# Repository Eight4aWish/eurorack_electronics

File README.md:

# Eurorack Electronics

Analog Eurorack breadboard layouts, a dual-channel low-pass gate, a mixed-signal MOD2 design (not built yet), a build-phase schematic generator, and a layout visualiser. Originally lived inside [Eight4aWish/eurorack_modules](https://github.com/Eight4aWish/eurorack_modules) — split out so that repo can stay focused on firmware.

## What's here

### `tools/n8layout/`

[n8synth](https://www.n8synth.com/) platform layout files: the official blank module templates (SVG with embedded n8 metadata) plus one worked example.

- `4HP Template.n8layout`, `6HP_Template.n8layout`, `10HP Template.n8layout`, `10HPS Template.n8layout` — official blank templates (10HPS = 10HP with a second stacked breadboard). These are the **source of truth for board geometry** — `tools/visualizer/gen_board_profiles.py` parses them into board-profile JSON.
- `808_Kick_Example.n8layout` — example 808-style kick layout

### `tools/visualizer/`

A browser-based layout viewer that renders breadboard placements from JSON, plus Python helpers for netlist → layout conversion and placement validation.

MIT ([LICENSE](tools/visualizer/LICENSE)), shared as it is. The exception is `layouts/boy_*`: they draw the analogue board, so they keep its CC BY-SA 4.0.

- `index.html` — main visualiser; opens any layout from `layouts/`
- `check.sh` — **one-command check**: geometry → net identity → browser wrapper regeneration → doc maps → doc-position cross-check. Refuses to regenerate docs from a failing layout.
- `netlist_to_layout.py` — netlist → layout JSON converter
- `smoke_test.py` — executes the visualiser's scripts against a stub DOM and asserts a layout registers; catches load-time errors that silently empty the layout picker
- `check_doc_positions.py` — every control position a doc names by hand must exist in the layout
- `edit_layout.py` — **hand-edit a layout from the bench**: move an endpoint (`b10 > g12`), set a component (`C15 = g12 g13`), mirror left/right, shift rows or ICs. Refuses any edit that would collide, then you re-run `check.sh`
- `check_netlist.py` — **every pin against a netlist**, following the wires: a row joining the wrong pins is a short, a wire left out is an open. Works on any layout, with no table to transcribe
- `cross_check_nets.py` / `validate_layout.py` / `sync_layout.py` / `gen_rowmap.py` — placement validation + maintenance helpers
- `bundle_skill.py` — copies the checks and viewer into the [n8synth-layout](https://github.com/Eight4aWish/eight4awish/tree/main/skills/n8synth-layout) Claude skill
- `gen_board_profiles.py` / `boards/` — board-profile JSON generated from the official n8synth templates: JPS control-deck cells, edge-connector maps, gap positions, D ground bus. **Ground truth for platform behaviour is [`docs/n8synth_platform.md`](docs/n8synth_platform.md)** — that document wins over anything inferred from the templates or these profiles.
- `layouts/` — per-module JS + JSON layouts

### How I use this (workflow)

The loop that produced the dual LPG, end to end:

1. **Reference review** — survey published schematics for the topology, compare sources, pick component values. Output: `docs/<module>_reference_review.md` + `docs/<module>_netlist.md` with named nets and per-source confidence tags.
2. **Skeleton layout** — `netlist_to_layout.py` converts the netlist doc into a layout JSON with components, stages, and net assignments but no positions.
3. **Placement** — fill in row/column positions per build phase (LLM-assisted in Claude Code sessions, guided by the board profile's control-deck maps in `boards/`). Panel-facing legs land on control-deck JPS pads; grounds tie to the deck-wide D bus.
4. **Verify** — `./check.sh`: zero hole collisions, every component on the nets the netlist requires, then the placement doc's row maps regenerate from the JSON so they can never drift.
5. **Build** — open the visualiser, step through the build phases at the bench; each phase carries its own test checklist (visible in the side panel).

Repeat 3–4 until clean; the layout JSON is always the single source of truth for placement.

To run locally:

```sh
# From this directory
python3 -m http.server 8000
# then open http://localhost:8000/tools/visualizer/
```

Or open `tools/visualizer/index.html` directly in a browser if you don't need module loading.

### `hardware/analogue_board/` and `tools/analogue_board/`

**The analogue board**: a general-purpose I/O board behind an n8synth Control Deck. **Rev A**, for a Teensy 4.1, was built and tested on 2026-11-01 and runs as Boy, whose firmware is in [`eurorack_modules`](https://github.com/Eight4aWish/eurorack_modules/blob/main/docs/TEENSY_MOVE.md). **Rev B**, the Pico 2 format for a Pico 2W or ESP32-P4, was ordered on 2026-11-03 (`hardware/analogue_board/pico_revb/`). Spec and decision log: [`docs/analogue_board_spec.md`](docs/analogue_board_spec.md). Rev A's firmware notes: [`docs/analogue_board_reva_firmware.md`](docs/analogue_board_reva_firmware.md). Rev B: [`docs/analogue_board_revb.md`](docs/analogue_board_revb.md).

- `hardware/analogue_board/`: the KiCad 9 project, the schematic PDF and the check results. Hardware licence CC BY-SA 4.0.
- `tools/analogue_board/build.py`: generates the schematic, runs KiCad's ERC, exports the PDF, netlist and BOM, and checks every IC pin against its datasheet, the netlist against intent, decoupling and diode orientation. See [`hardware/analogue_board/README.md`](hardware/analogue_board/README.md).

### `tools/noise_test/`

The noise comparison of five audio boards (the old Boy, Boy Rev A, the stock and OLED patch.inits, the hand-built Seed module) with the screen off, still and redrawing: `record.py` records a run through the ES-10, `analyse.py` turns it into A-weighted noise, hum, spurs and the input's share. Method, what to plug and the procedure: [`docs/noise_test.md`](docs/noise_test.md). The test firmware is in `eurorack_daisy_patch_init/noise_test` and `eurorack_modules/src/noise_test`.

### `tools/schematic/`

Build-phase schematic generator for the **Dual Pingable LPG**. Produces per-phase PNGs (Phase 1 / Phase 2 / Mix) into `docs/schematics/`, with component values read live from the LPG layout JSON so the diagrams stay in sync with the design. Built on [Schemdraw](https://schemdraw.readthedocs.io/). See [`tools/schematic/README.md`](tools/schematic/README.md).

### `docs/`

Circuit notes, netlists, and reference material.

**Plans**

- `public_tool_plan.md` — plan for a third-party-usable version of the placement/visualisation
  tooling, with the dual LPG and the MOD2/Melon hybrid as the two flagship examples.

**Platform reference**

- `n8synth_platform.md` — verified electrical behaviour of the n8synth breadboards and control
  decks: main area vs edge connector vs power rail, board variants, grounding practice. The
  single source of truth; everything else is downstream of it.

**Dual Pingable LPG** — original dual-channel low-pass gate (canonical Buchla 292 audio path + Strike + CV + Depth + mix output):

- `lpg_reference_review.md` — topology survey, target feature set, vactrol part choices
- `lpg_published_schematics.md` — comparison of the source schematics that informed the design
- `lpg_netlist.md` — full netlist
- `lpg_breadboard_placement.md` — n8synth placement, panel layout, build-phase order
- `lpg_mod_pot_rerange.md` — step-by-step bench procedure for the rev 0.27 DEPTH/MANUAL re-range (proposed, not yet built), written for picking the board up cold
- `lpg_bom.csv` — bill of materials
- `schematics/` — generated build-phase PNGs

Reference materials that informed the LPG design are linked at their original sources (see Credits) rather than redistributed here.

## Credits

### Dual Pingable LPG

The audio path is the canonical **Buchla 292** Lopass Gate, originally designed by **Don Buchla** (~1971). The topology, component values, and driver structure of this build were cross-validated against multiple independent published sources, each linked at its original home:

- **Parker, J. & D'Angelo, S.** — *"A Digital Model of the Buchla Lowpass-Gate"*, [DAFx 2013](https://www.dafx.de/paper-archive/details.php?id=uqLQLFI9j52bBmv10UKKMg) — the analytic topology and closed-form gains (Rα placement per Eq. 4 / Eq. 12).
- **Nonlinear Circuits (NLC) [Low Pass Gate](https://www.nonlinearcircuits.com/modules/p/low-pass-gate)** — Rα = 4M7, 470R LED current limit, the zener clamp on the LED-drive node (VD5 / VD6).
- **AI Synthesis [AI017 Low Pass Gate](https://aisynthesis.com/product/ai017-low-pass-gate/)** — 10K series resistors flanking the vactrol LDRs, DEPTH wired as a rheostat (their P3).
- **Eddy Bergmann's redrawn Buchla 292** — [Synthesizer Build part-35: Resonant Lopass Gate](https://www.eddybergman.com/2020/10/synthesizer-build-part-35-resonant.html) — confirmed the Rα placement and the 1K series output resistor (R_OUT_A / R_OUT_B).
- **Thomas White's [NRM Lopass Gate](https://modularsynthesis.com/nrm/lopass/lopass.htm)** — third independent confirmation of Rα at V₊ → GND.
- **Doepfer [A-101-2 Low Pass Gate](https://doepfer.de/a1012.htm)** — the "status LED tracks vactrol drive" concept (adapted here to a parallel branch off the driver, rather than series, for compatibility across vactrol / LED options).

Target feature set (dual-channel, Strike-pingable, no DAMP / mode-switch in the day-one core) follows the **Make Noise Optomix / LxD** shape; see [lpg_reference_review.md](docs/lpg_reference_review.md) for the topology survey and trade-offs. Per-source confidence tags and the rationale for each block are in [lpg_netlist.md](docs/lpg_netlist.md) and [lpg_published_schematics.md](docs/lpg_published_schematics.md).

## Companion repo

Firmware for Eurorack modules using these analog voices and layouts lives in [Eight4aWish/eurorack_modules](https://github.com/Eight4aWish/eurorack_modules). Per-module pre-built binaries are published as releases there.

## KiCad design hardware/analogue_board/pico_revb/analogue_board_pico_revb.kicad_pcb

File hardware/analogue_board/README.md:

# Analogue boards, Rev A

General-purpose Eurorack I/O boards. A compute module sits on headers on one side, an n8synth
Control Deck on the other, and every audio, CV, gate, pot and display interface sits in between.
Rev A is **two boards** from one design (2026-10-16):

| Board | Module | Folder |
|---|---|---|
| Pico board | Raspberry Pi Pico 2, or a Waveshare ESP32-P4-WIFI6 in its pinout | [`pico/`](pico/) |
| Teensy board | Teensy 4.1, all 48 pins on standard headers | [`teensy/`](teensy/) |

Both boards share the peripheral circuits, pin functions, wiring field, edge strips and power
corner, so firmware and panel wiring are the same on both. The design brief and every decision
behind it are in [`docs/analogue_board_spec.md`](../../docs/analogue_board_spec.md).

Two more builds from the same generator are routing trials, not boards to order:

| Trial | What it is | Folder |
|---|---|---|
| Shared board | Both module footprints interleaved on one board, as checkpoint 2 had it; the Teensy on shortened headers | [`shared/`](shared/) |
| Core board | The Pico board without the fixed-direction CV channels, TRS MIDI or the Qwiic socket, with six pots; parts 0.4 mm apart, 0.127 mm signal rules. The first to route (spec §14); its routed board is in [`pico_core/routed_trial/`](pico_core/routed_trial/) | [`pico_core/`](pico_core/) |
| Shared core board | Both module sockets (the Teensy on full headers), TRS MIDI, the display on I2C holes, six switchable CV jacks, six pots, four gates each way. Four routes in a row ended 2 connections short, a different 2 each time; its first routed board is in [`shared_core/routed_trial/`](shared_core/routed_trial/) | [`shared_core/`](shared_core/) |
| **Pico core board with MIDI** | The same feature set on a Pico 2 / ESP32-P4 board alone: module 8 mm lower, no bus test points, +5VD plane on In4, top of the board re-laid by David with no chip over another. **Fully routed** (0 unconnected, 0 copper faults); routed board in [`pico_core_midi/routed_trial/`](pico_core_midi/routed_trial/), order files in [`pico_core_midi/fab/`](pico_core_midi/fab/), held until the Teensy board is brought up | [`pico_core_midi/`](pico_core_midi/) |
| **Teensy core board with MIDI** | **The first board to route completely:** the same feature set on a Teensy 4.1 board alone, placement revised by eye. 0 unconnected, 0 copper faults; its routed board is in [`teensy_core_midi/routed_trial/`](teensy_core_midi/routed_trial/) | [`teensy_core_midi/`](teensy_core_midi/) |
| **Rev B, Pico 2 / ESP32-P4** | Laid out panel first ([`docs/analogue_board_revb.md`](../../docs/analogue_board_revb.md)): one wiring template level with the deck's cells, the ESP32-P4's own I2C reserved, 10HP only, the power header in the lower gap. **Fully routed** (0 unconnected, 0 copper faults, every IC supply pin within 4 mm of a capacitor); routed board in [`pico_revb/routed_trial/`](pico_revb/routed_trial/). Order after the Teensy board's bring-up | [`pico_revb/`](pico_revb/) |

**Status: checkpoint 4, 2026-10-16.** `teensy_core_midi` routes completely: KiCad's DRC finds
no unconnected item and no copper fault, every surface-mount ground pad has its own via to the
plane, and 54 decoupling capacitors are wired straight to their pins. Its wiring blocks and test
points are labelled, the wiring map is in `teensy_core_midi/output/wiring_map.md`, and the JLCPCB
files are in [`teensy_core_midi/fab/`](teensy_core_midi/fab/): **ordered 2026-10-16** (5 boards,
2 assembled). `pico_core_midi` routes completely too (2026-10-17); its order waits on the Teensy
board's bring-up, so any Rev A lessons go into it first. The spec's §14 has every trial; the
story is in [`docs/analogue_board_journal.md`](../../docs/analogue_board_journal.md).
- **Schematic history:** it passed checkpoint 1 as a single board with both module footprints.
  The split changed only the root sheet (one module) and the power sheet, where the ESP32-P4
  bypass (Q201, JP201) stays on the Pico board.

## What's here

| File | What it is |
|---|---|
| `pico/`, `teensy/` | One KiCad 9 project per board. Each folder holds: |
| ↳ `analogue_board_<board>_schematic.pdf` | The schematic, 10 A3 sheets. Sheet 1 is the module and its pin map |
| ↳ `analogue_board_<board>.kicad_pcb` | Checkpoint 3: every part placed on both faces; not yet routed |
| ↳ `output/placement_outward_face.pdf`, `output/placement_deck_face.pdf` | Placement drawings: every part's outline, pads and reference, one face per PDF (vector, zoom in). The deck face is mirrored, as seen from the deck side |
| ↳ `output/placement_outward_face.png`, `output/placement_deck_face.png` | 3D renders of both faces (the deck face seen from below, so mirrored) |
| ↳ `output/checks.md` | Every checkpoint-1 check and its result: ERC, netlist, pins against datasheets, footprints, decoupling, diode orientation |
| ↳ `output/erc.rpt`, `output/*.net`, `output/*_bom.csv` | KiCad's ERC report, netlist and grouped BOM with LCSC numbers |
| `analogue_board.kicad_sym`, `analogue_board.pretty/` | Project symbols and footprints, shared by both boards: DAC8568, Pico 2, Teensy 4.1, edge strip, module sockets, edge strips, wiring holes |
| [`boards_printout.pdf`](boards_printout.pdf) | 1:1 printout (A4, print at 100 %) of each board's outline, edge strips, module socket, USB keep-out and power header, to lay real parts on |
| [`checkpoint2_printout.pdf`](checkpoint2_printout.pdf) | The checkpoint 2 printout, from when both modules shared one board (kept as the record) |
| [`LICENSE`](LICENSE) | CC BY-SA 4.0 |

## The boards are generated

The KiCad files are written by [`tools/analogue_board/`](../../tools/analogue_board/). Change the
generator, not the KiCad files, until the boards are signed off. After that the KiCad files
become the source and the generator is retired.

```sh
python3 tools/analogue_board/build.py      # schematics, ERC, netlists, PDFs, checks (both boards)
python3 tools/analogue_board/pcb.py        # the boards: placement, DRC, renders (both boards)
python3 tools/analogue_board/build.py teensy   # or one board: pico or teensy
```

`build.py` regenerates the libraries and all ten sheets. It then runs KiCad's ERC, exports the
PDF, netlist and BOM through `kicad-cli`, and runs the checks. It exits non-zero if any check
fails. It needs KiCad 9 at `/Applications/KiCad` and Python 3, nothing else.

| Generator file | Holds |
|---|---|
| `variant.py` | Which board a run builds (`pico`, `teensy`, the trials `shared`, `pico_core`, `shared_core`, `pico_core_midi` and `teensy_core_midi`, and Rev B's `pico_revb`): folders, module sockets, feature set, placement spacing, track rules, the module's position and the power header's |
| `design.py` | Pin map, root sheet (this board's module), power sheet |
| `design_analog.py` | Codec and audio, CV jacks and ADC, CV DAC |
| `design_digital.py` | Pots and gate outs, expander/I2C/LEDs, gate ins and jack detect, edge strips, TRS MIDI |
| `parts.py` | Every part: symbol, footprint, LCSC number, datasheet |
| `datasheet_pins.json` | Each IC's pinout transcribed from its datasheet, independently of KiCad's library. `checks.py` compares the two. |
| `checks.py` | The checkpoint-1 checks |
| `placement.py` | Geometry: outline, strips, module positions, keep-outs, power header, and each board's floorplan |
| `wiring.py` | The wiring field: every channel hole, its bank (four mixed banks, one per quarter of the board) and its slot. The schematic and the placement both read it |
| `pcb.py` | Writes each board from its netlist and `placement.py`. It prints the area budget, runs DRC with the schematic-parity check, checks part heights and renders both faces |
| `autoplace.py` | First-pass placement of every part `placement.py` does not anchor, as close as it fits to the pins it connects to |
| `autoroute.py` | Autoroute with Freerouting. Runs under KiCad's Python and writes a separate trial board in `<board>/output/autoroute/` (not committed). Takes 4 or 6 layers, a run label and any Freerouting setting. `--staged` runs the stages (`--stages=2` stops after the second); `--ground-vias` gives every surface-mount ground pad its own via first, `--decoupling` wires each decoupling capacitor to its pin first; `--lock-existing` and `--unlock` set what the router may rip up. Freerouting's analytics are switched off |
| `finish.py` | Finishes a routed board: via drills, narrow tracks, copper faults taken up, the leftover connections routed by its own grid router and then by rip-up and reroute, dead ends removed, ground pads stitched. Also holds the pre-route steps `autoroute.py` calls |
| `labels.py` | Silkscreen on a routed board: block numbers W1, W2 ... beside the wiring blocks, short names beside the test points; writes `output/wiring_map.md` (every block's holes and signals, every test point) and 1:1 PDFs of each face to print |
| `fab.py` | JLCPCB files from a finished board: Gerbers and drill zipped, BOM and placement (CPL) in JLC's format, into `<board>/fab/` |
| `printout.py` | Writes `boards_printout.pdf` |

The netlist check works from intent. Every connection the generator draws is also recorded as
"pin X belongs on net Y". The check then compares those records with the netlist KiCad computes.
A wire that lands on the wrong pin, two nets that touch, or a pin nobody meant to connect all
fail the build.

## Wiring field conventions

- Every wiring hole is round, except **ground holes, which are square**.
- The headers keep KiCad's square pin 1: the module socket, the edge strips' outer holes, and
  J201, where pin 1 is −12 V (the red stripe).

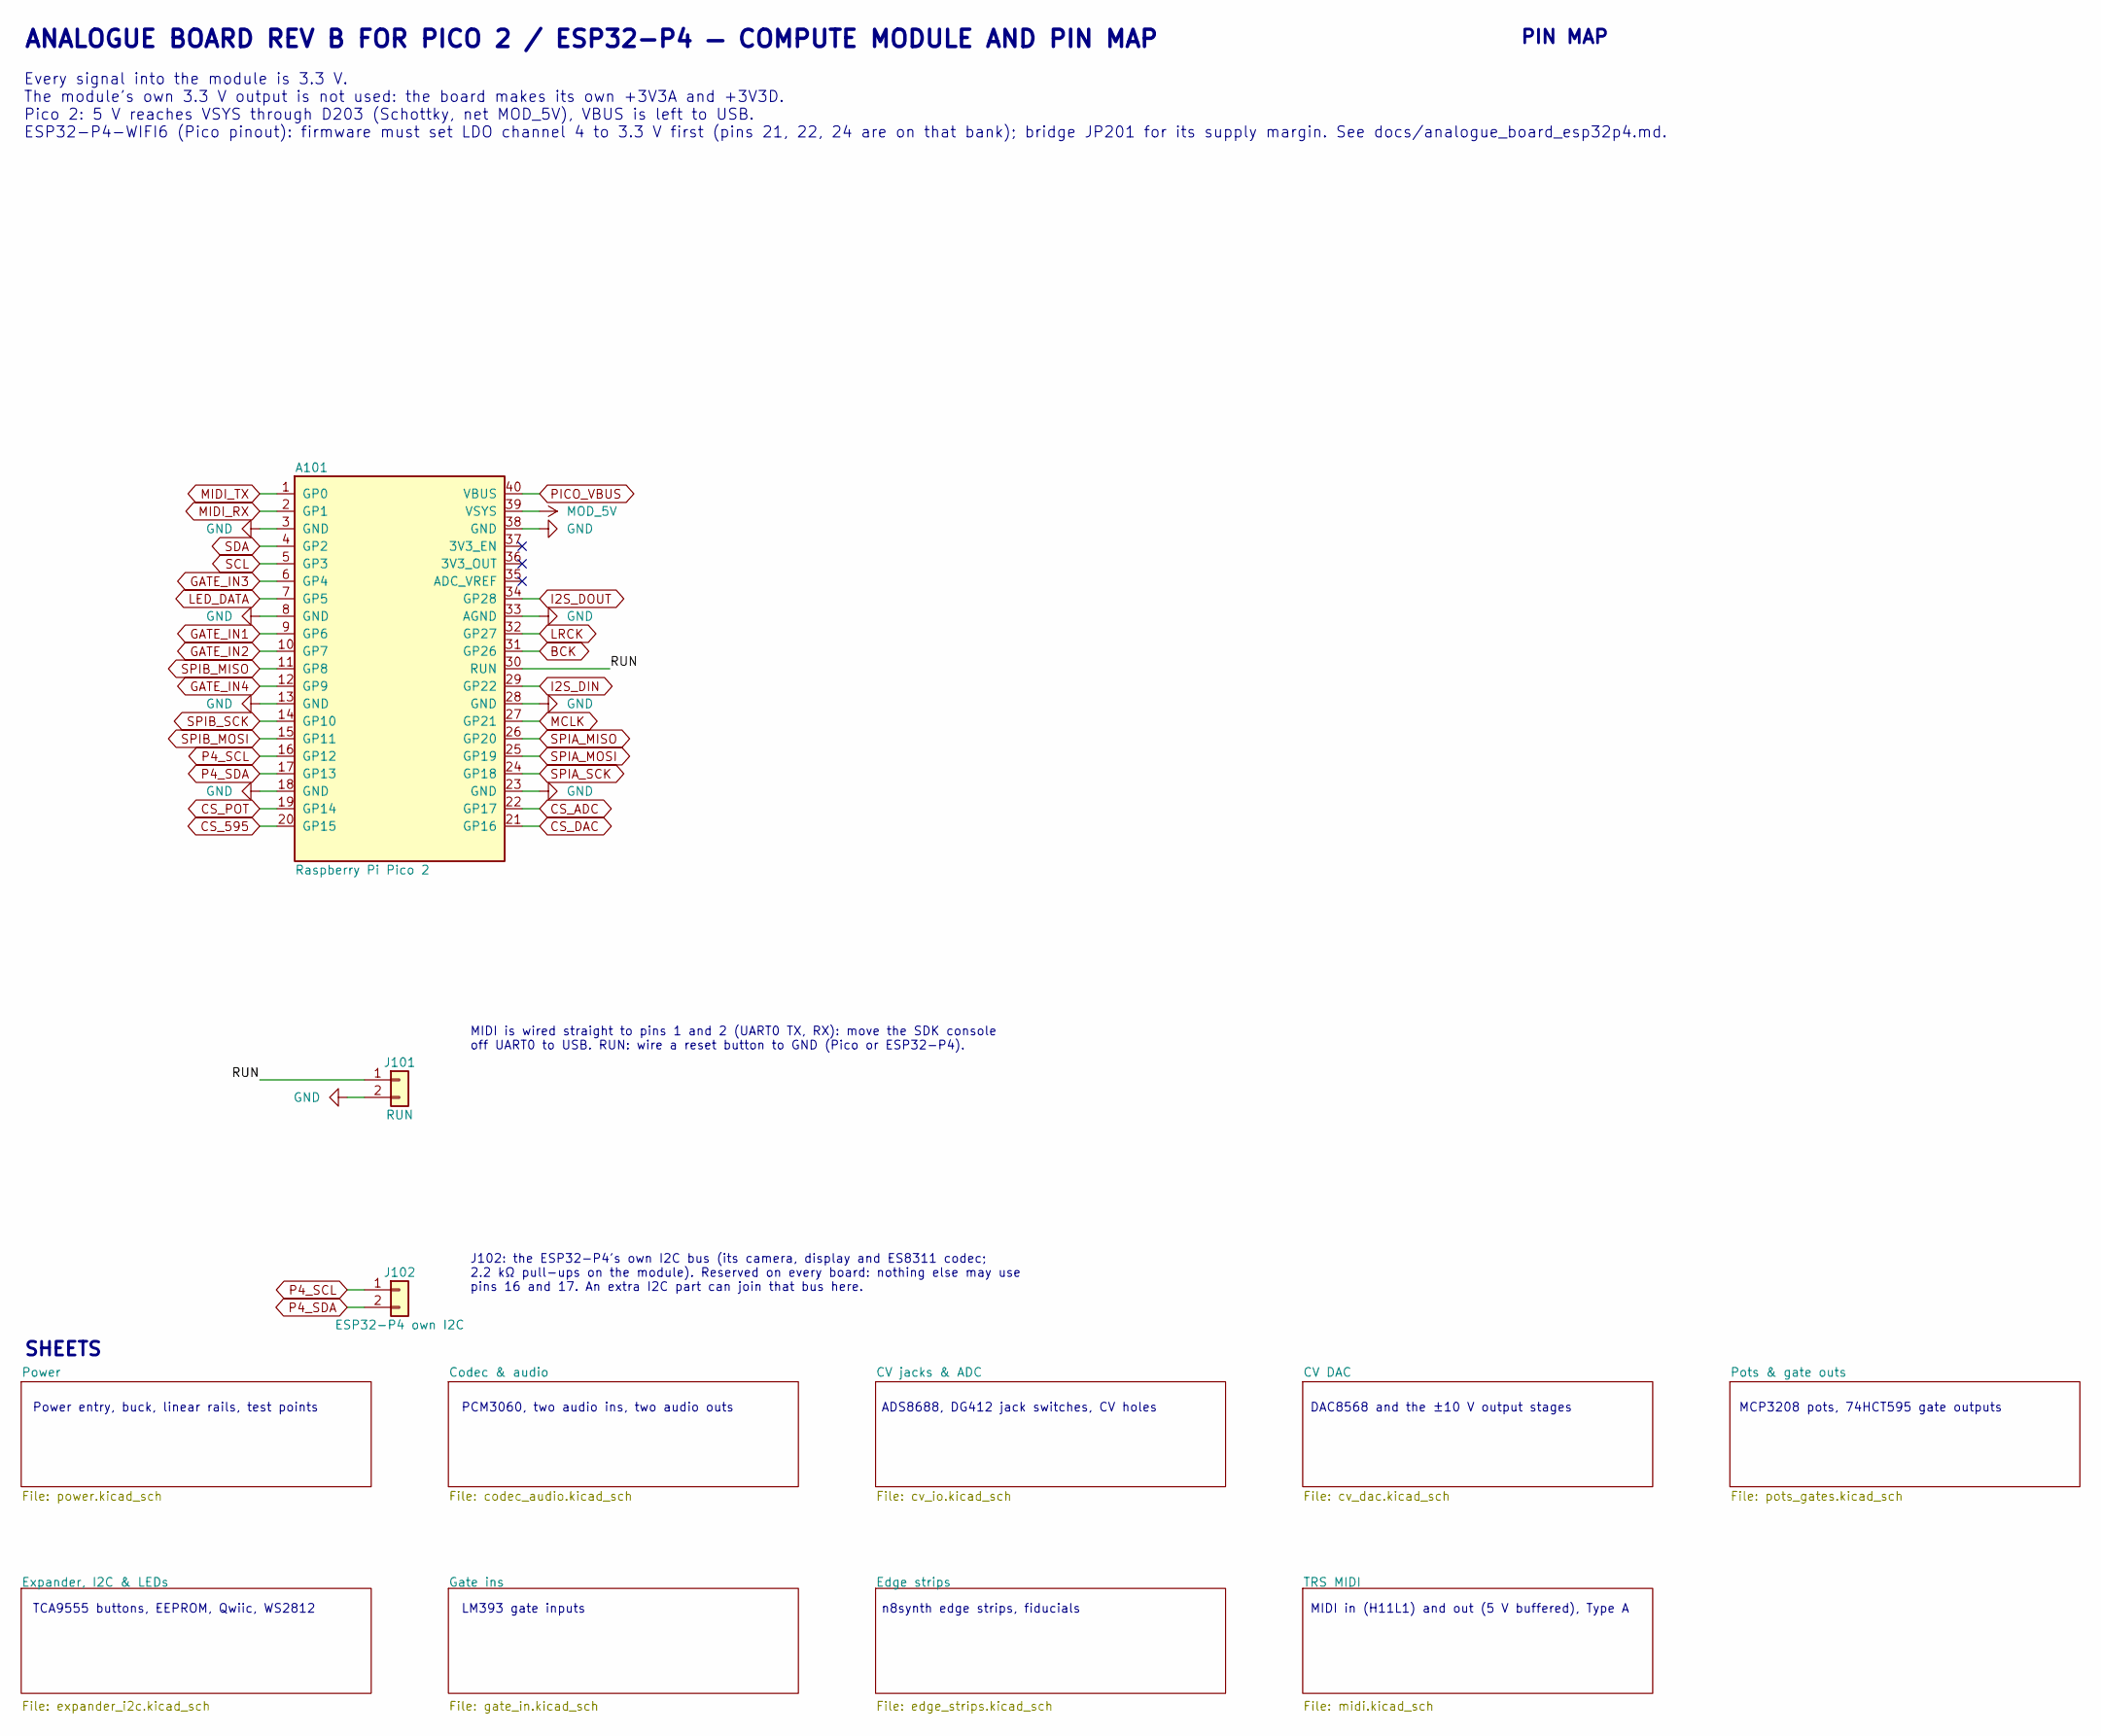
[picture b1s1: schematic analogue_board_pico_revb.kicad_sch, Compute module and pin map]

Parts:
A101: Raspberry Pi Pico 2; Pico2_Socket; MPN SC1631 on 2x20 female headers; JLC hand-soldered
J101: RUN; WiringHoles_1x02_G2; JLC bare holes
J102: ESP32-P4 own I2C; WiringHoles_1x02; JLC bare holes

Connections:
/RUN: A101.30 (RUN), J101.1
BCK: A101.31 (GP26); also elsewhere on the board
CS_595: A101.20 (GP15); also elsewhere on the board
CS_ADC: A101.22 (GP17); also elsewhere on the board
CS_DAC: A101.21 (GP16); also elsewhere on the board
CS_POT: A101.19 (GP14); also elsewhere on the board
GATE_IN1: A101.9 (GP6); also elsewhere on the board
GATE_IN2: A101.10 (GP7); also elsewhere on the board
GATE_IN3: A101.6 (GP4); also elsewhere on the board
GATE_IN4: A101.12 (GP9); also elsewhere on the board
GND: A101.3 (GND), A101.8 (GND), A101.13 (GND), A101.18 (GND), A101.23 (GND), A101.28 (GND), A101.33 (AGND), A101.38 (GND), J101.2; also elsewhere on the board
I2S_DIN: A101.29 (GP22); also elsewhere on the board
I2S_DOUT: A101.34 (GP28); also elsewhere on the board
LED_DATA: A101.7 (GP5); also elsewhere on the board
LRCK: A101.32 (GP27); also elsewhere on the board
MCLK: A101.27 (GP21); also elsewhere on the board
MIDI_RX: A101.2 (GP1); also elsewhere on the board
MIDI_TX: A101.1 (GP0); also elsewhere on the board
MOD_5V: A101.39 (VSYS); also elsewhere on the board
P4_SCL: A101.16 (GP12), J102.1
P4_SDA: A101.17 (GP13), J102.2
PICO_VBUS: A101.40 (VBUS); also elsewhere on the board
SCL: A101.5 (GP3); also elsewhere on the board
SDA: A101.4 (GP2); also elsewhere on the board
SPIA_MISO: A101.26 (GP20); also elsewhere on the board
SPIA_MOSI: A101.25 (GP19); also elsewhere on the board
SPIA_SCK: A101.24 (GP18); also elsewhere on the board
SPIB_MISO: A101.11 (GP8); also elsewhere on the board
SPIB_MOSI: A101.15 (GP11); also elsewhere on the board
SPIB_SCK: A101.14 (GP10); also elsewhere on the board

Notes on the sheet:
ANALOGUE BOARD REV B FOR PICO 2 / ESP32-P4 — COMPUTE MODULE AND PIN MAP
Every signal into the module is 3.3 V. The module's own 3.3 V output is not used: the board makes its own +3V3A and +3V3D. Pico 2: 5 V reaches VSYS through D203 (Schottky, net MOD_5V), VBUS is left to USB. ESP32-P4-WIFI6 (Pico pinout): firmware must set LDO channel 4 to 3.3 V first (pins 21, 22, 24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
MIDI is wired straight to pins 1 and 2 (UART0 TX, RX): move the SDK console off UART0 to USB. RUN: wire a reset button to GND (Pico or ESP32-P4).
J102: the ESP32-P4's own I2C bus (its camera, display and ES8311 codec; 2.2 kΩ pull-ups on the module). Reserved on every board: nothing else may use pins 16 and 17. An extra I2C part can join that bus here.
PIN MAP
Power entry, buck, linear rails, test points
PCM3060, two audio ins, two audio outs
ADS8688, DG412 jack switches, CV holes
DAC8568 and the ±10 V output stages
MCP3208 pots, 74HCT595 gate outputs
TCA9555 buttons, EEPROM, Qwiic, WS2812
LM393 gate inputs
n8synth edge strips, fiducials
MIDI in (H11L1) and out (5 V buffered), Type A
SHEETS

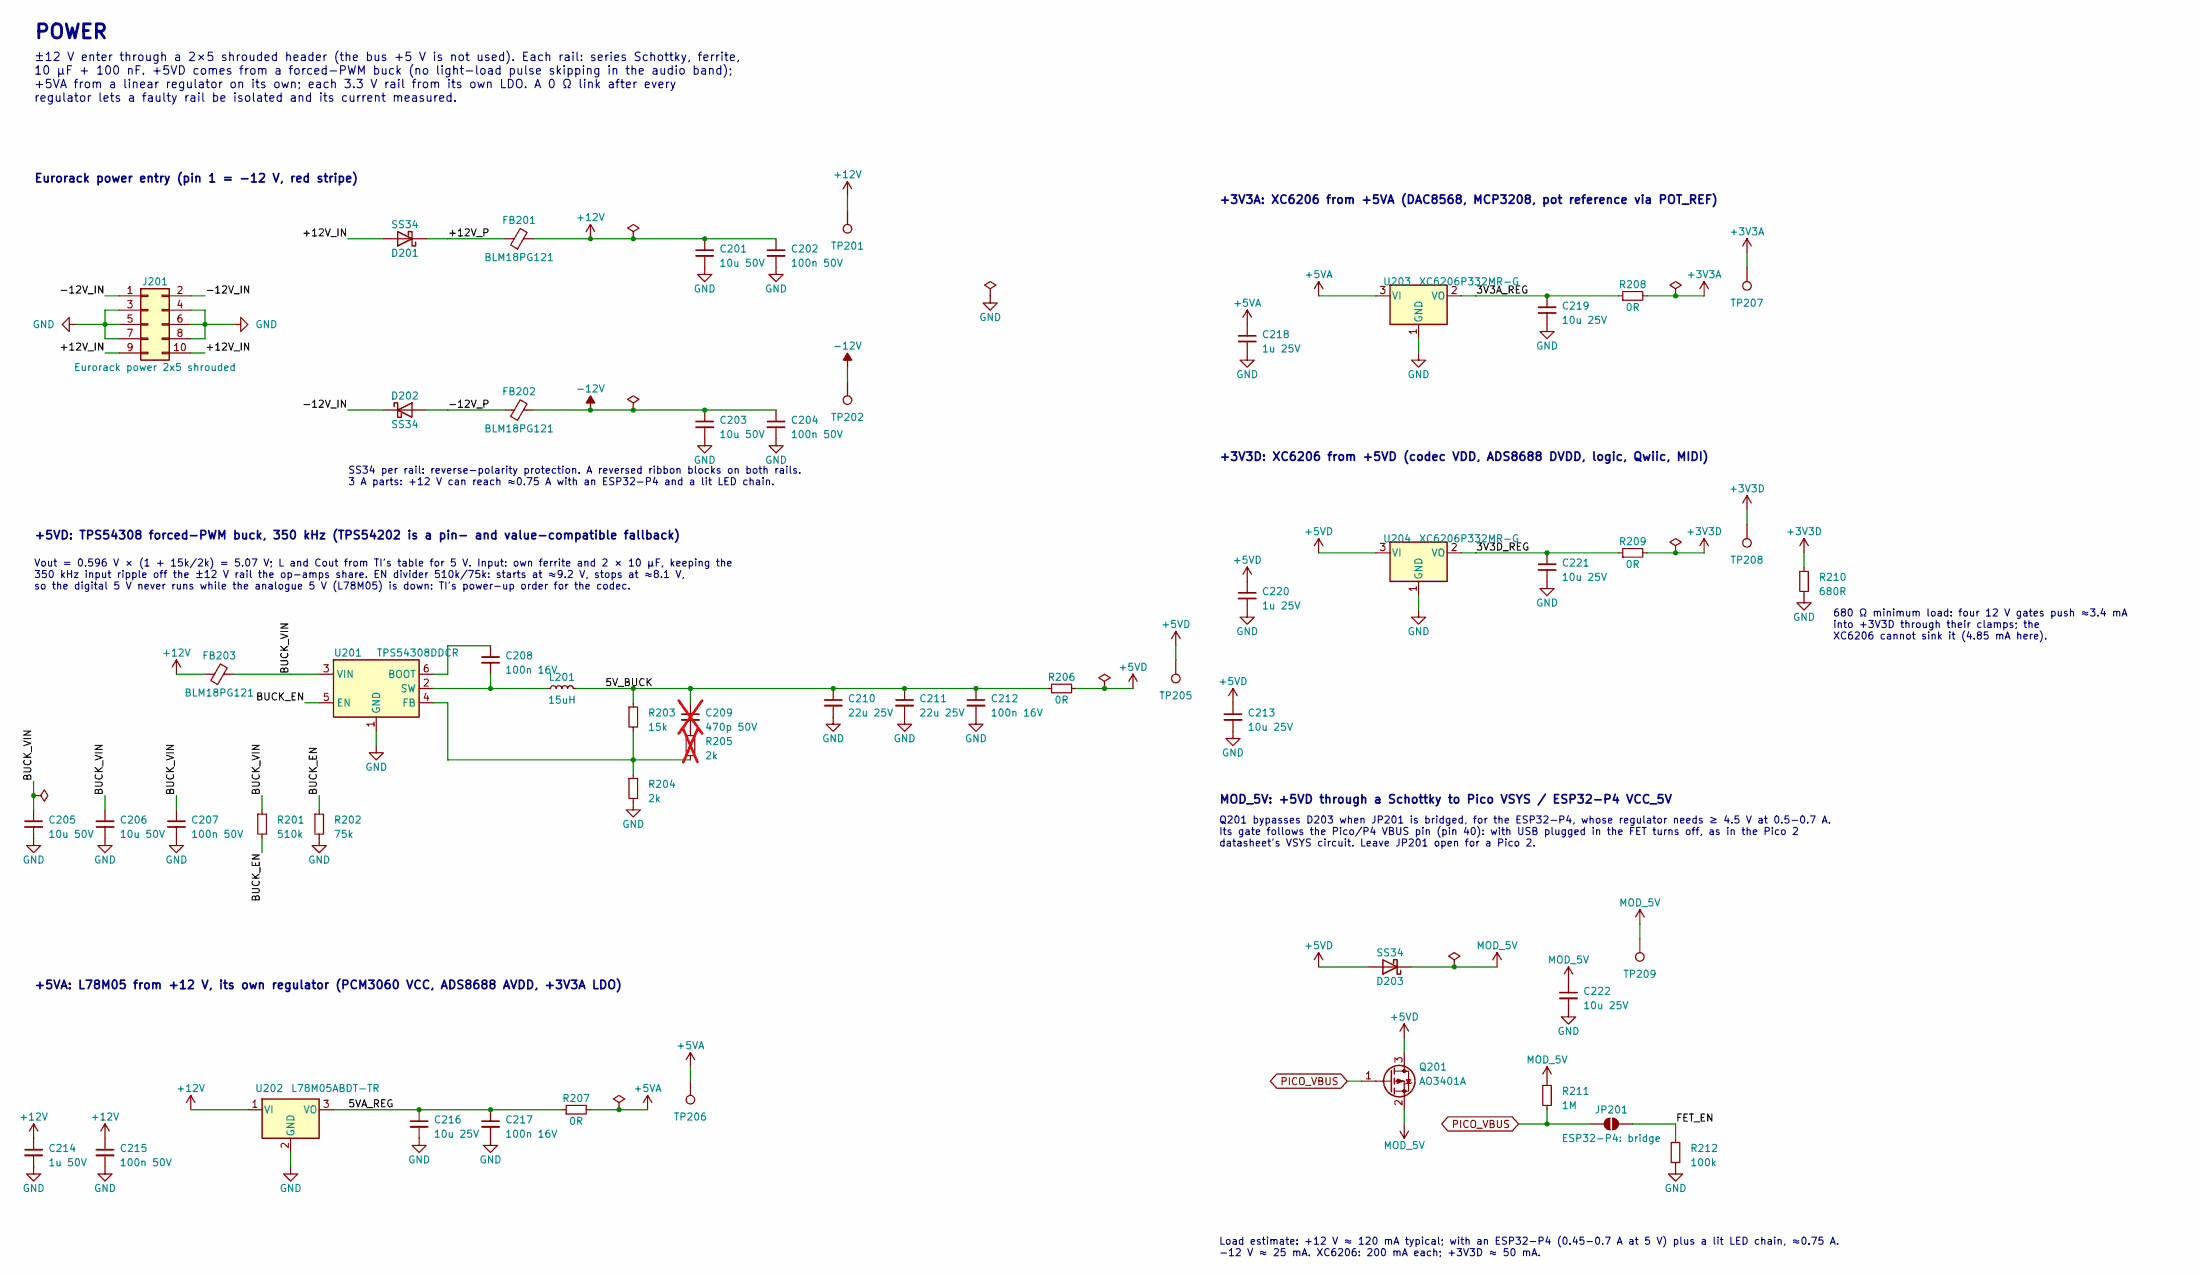
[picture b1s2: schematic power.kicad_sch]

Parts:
C201, C203, C205, C206: 10u 50V; C_1206_3216Metric; Voltage 50V; LCSC C13585
C202, C204, C207, C215: 100n 50V; C_0603_1608Metric; Voltage 50V; LCSC C14663
C208, C212, C217: 100n 16V; C_0402_1005Metric; Voltage 16V; LCSC C1525
C209: 470p 50V; C_0402_1005Metric; Voltage 50V; JLC not fitted; not fitted
C210, C211: 22u 25V; C_1206_3216Metric; Voltage 25V; LCSC C12891
C213, C216, C219, C221, C222: 10u 25V; C_0805_2012Metric; Voltage 25V; LCSC C15850
C214: 1u 50V; C_0603_1608Metric; Voltage 50V; LCSC C15849
C218, C220: 1u 25V; C_0402_1005Metric; Voltage 25V; LCSC C52923
D201, D202, D203: SS34; D_SMA; MPN SS34; LCSC C8678
FB201, FB202, FB203: BLM18PG121; L_0603_1608Metric; MPN BLM18PG121SN1D; LCSC C14709
J201: Eurorack power 2x5 shrouded; IDC-Header_2x05_P2.54mm_Vertical; MPN 2x5 2.54 mm shrouded box header; JLC hand-soldered
JP201: ESP32-P4: bridge; SolderJumper-2_P1.3mm_Open_RoundedPad1.0x1.5mm; JLC bare pad
L201: 15uH; L_Sunlord_SWPA5040S; MPN SWPA5040S150MT; LCSC C44888
Q201: AO3401A; SOT-23; MPN AO3401A; LCSC C15127
R201: 510k; R_0603_1608Metric; Tolerance 1%; LCSC C23192
R202: 75k; R_0603_1608Metric; Tolerance 1%; LCSC C23242
R203: 15k; R_0402_1005Metric; Tolerance 1%; LCSC C25756
R204: 2k; R_0402_1005Metric; Tolerance 1%; LCSC C4109
R205: 2k; R_0402_1005Metric; Tolerance 1%; LCSC C4109; not fitted
R206: 0R; R_0805_2012Metric; Tolerance 1%; LCSC C17477
R207, R208, R209: 0R; R_0603_1608Metric; Tolerance 1%; LCSC C21189
R210: 680R; R_0603_1608Metric; Tolerance 1%; LCSC C23228
R211: 1M; R_0402_1005Metric; Tolerance 1%; LCSC C26083
R212: 100k; R_0402_1005Metric; Tolerance 1%; LCSC C25741
TP201: +12V; TestPoint_Pad_D1.0mm; JLC bare pad
TP202: -12V; TestPoint_Pad_D1.0mm; JLC bare pad
TP205: +5VD; TestPoint_Pad_D1.0mm; JLC bare pad
TP206: +5VA; TestPoint_Pad_D1.0mm; JLC bare pad
TP207: +3V3A; TestPoint_Pad_D1.0mm; JLC bare pad
TP208: +3V3D; TestPoint_Pad_D1.0mm; JLC bare pad
TP209: MOD_5V; TestPoint_Pad_D1.0mm; JLC bare pad
U201: TPS54308DDCR; SOT-23-6; MPN TPS54308DDCR; LCSC C168839
U202: L78M05ABDT-TR; TO-252-2_PasteShapes; MPN L78M05ABDT-TR; LCSC C58069
U203, U204: XC6206P332MR-G; SOT-23; MPN XC6206P332MR-G; LCSC C5446

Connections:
+3V3A: R208.2, TP207.1; also elsewhere on the board
+3V3D: R209.2, R210.1, TP208.1; also elsewhere on the board
+5VA: C218.1, R207.2, TP206.1, U203.3 (VI); also elsewhere on the board
+5VD: C213.1, C220.1, D203.2 (A), Q201.3 (D), R206.2, TP205.1, U204.3 (VI); also elsewhere on the board
+12V: C201.1, C202.1, C214.1, C215.1, FB201.2, FB203.1, TP201.1, U202.1 (VI); also elsewhere on the board
-12V: C203.1, C204.1, FB202.2, TP202.1; also elsewhere on the board
/Power/3V3A_REG: C219.1, R208.1, U203.2 (VO)
/Power/3V3D_REG: C221.1, R209.1, U204.2 (VO)
/Power/5VA_REG: C216.1, C217.1, R207.1, U202.3 (VO)
/Power/5V_BUCK: C209.1, C210.1, C211.1, C212.1, L201.2, R203.1, R206.1
/Power/+12V_IN: D201.2 (A), J201.9, J201.10
/Power/+12V_P: D201.1 (K), FB201.1
/Power/-12V_IN: D202.1 (K), J201.1, J201.2
/Power/-12V_P: D202.2 (A), FB202.1
/Power/BUCK_EN: R201.2, R202.1, U201.5 (EN)
/Power/BUCK_VIN: C205.1, C206.1, C207.1, FB203.2, R201.1, U201.3 (VIN)
/Power/FET_EN: JP201.2 (B), R212.1
GND: C201.2, C202.2, C203.2, C204.2, C205.2, C206.2, C207.2, C210.2, C211.2, C212.2, C213.2, C214.2, C215.2, C216.2, C217.2, C218.2, C219.2, C220.2, C221.2, C222.2, J201.3, J201.4, J201.5, J201.6, J201.7, J201.8, R202.2, R204.2, R210.2, R212.2, U201.1 (GND), U202.2 (GND), U203.1 (GND), U204.1 (GND); also elsewhere on the board
MOD_5V: C222.1, D203.1 (K), Q201.2 (S), R211.1, TP209.1; also elsewhere on the board
unnamed: C209.2, R205.1
unnamed: C208.1, U201.6 (BOOT)
unnamed: R203.2, R204.1, R205.2, U201.4 (FB)
unnamed: C208.2, L201.1, U201.2 (SW)
PICO_VBUS: JP201.1 (A), Q201.1 (G), R211.2; also elsewhere on the board

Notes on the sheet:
POWER
±12 V enter through a 2×5 shrouded header (the bus +5 V is not used). Each rail: series Schottky, ferrite, 10 µF + 100 nF. +5VD comes from a forced-PWM buck (no light-load pulse skipping in the audio band); +5VA from a linear regulator on its own; each 3.3 V rail from its own LDO. A 0 Ω link after 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
Eurorack power entry (pin 1 = -12 V, red stripe)
SS34 per rail: reverse-polarity protection. A reversed ribbon blocks on both rails. 3 A parts: +12 V can reach ≈0.75 A with an ESP32-P4 and a lit LED chain.
+5VD: TPS54308 forced-PWM buck, 350 kHz (TPS54202 is a pin- and value-compatible fallback)
Vout = 0.596 V × (1 + 15k/2k) = 5.07 V; L and Cout from TI's table for 5 V. Input: own ferrite and 2 × 10 µF, keeping the 350 kHz input ripple off the ±12 V rail the op-amps share. EN divider 510k/75k: starts at ≈9.2 V, stops at ≈8.1 V, so the digital 5 V never runs while the analogue 5 V (L78M05) 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
+5VA: L78M05 from +12 V, its own regulator (PCM3060 VCC, ADS8688 AVDD, +3V3A LDO)
+3V3A: XC6206 from +5VA (DAC8568, MCP3208, pot reference via POT_REF)
+3V3D: XC6206 from +5VD (codec VDD, ADS8688 DVDD, logic, Qwiic, MIDI)
680 Ω minimum load: four 12 V gates push ≈3.4 mA into +3V3D through their clamps; the XC6206 cannot sink it (4.85 mA here).
MOD_5V: +5VD through a Schottky to Pico VSYS / ESP32-P4 VCC_5V
Q201 bypasses D203 when JP201 is bridged, for the ESP32-P4, whose regulator needs ≥ 4.5 V at 0.5-0.7 A. Its gate follows the Pico/P4 VBUS pin (pin 40): with USB plugged in the FET turns off, as in the Pico 2 datasheet's VSYS circuit. Leave JP201 open for a Pico 2.
Load estimate: +12 V ≈ 120 mA typical; with an ESP32-P4 (0.45-0.7 A at 5 V) plus a lit LED chain, ≈0.75 A. -12 V ≈ 25 mA. XC6206: 200 mA each; +3V3D ≈ 50 mA.

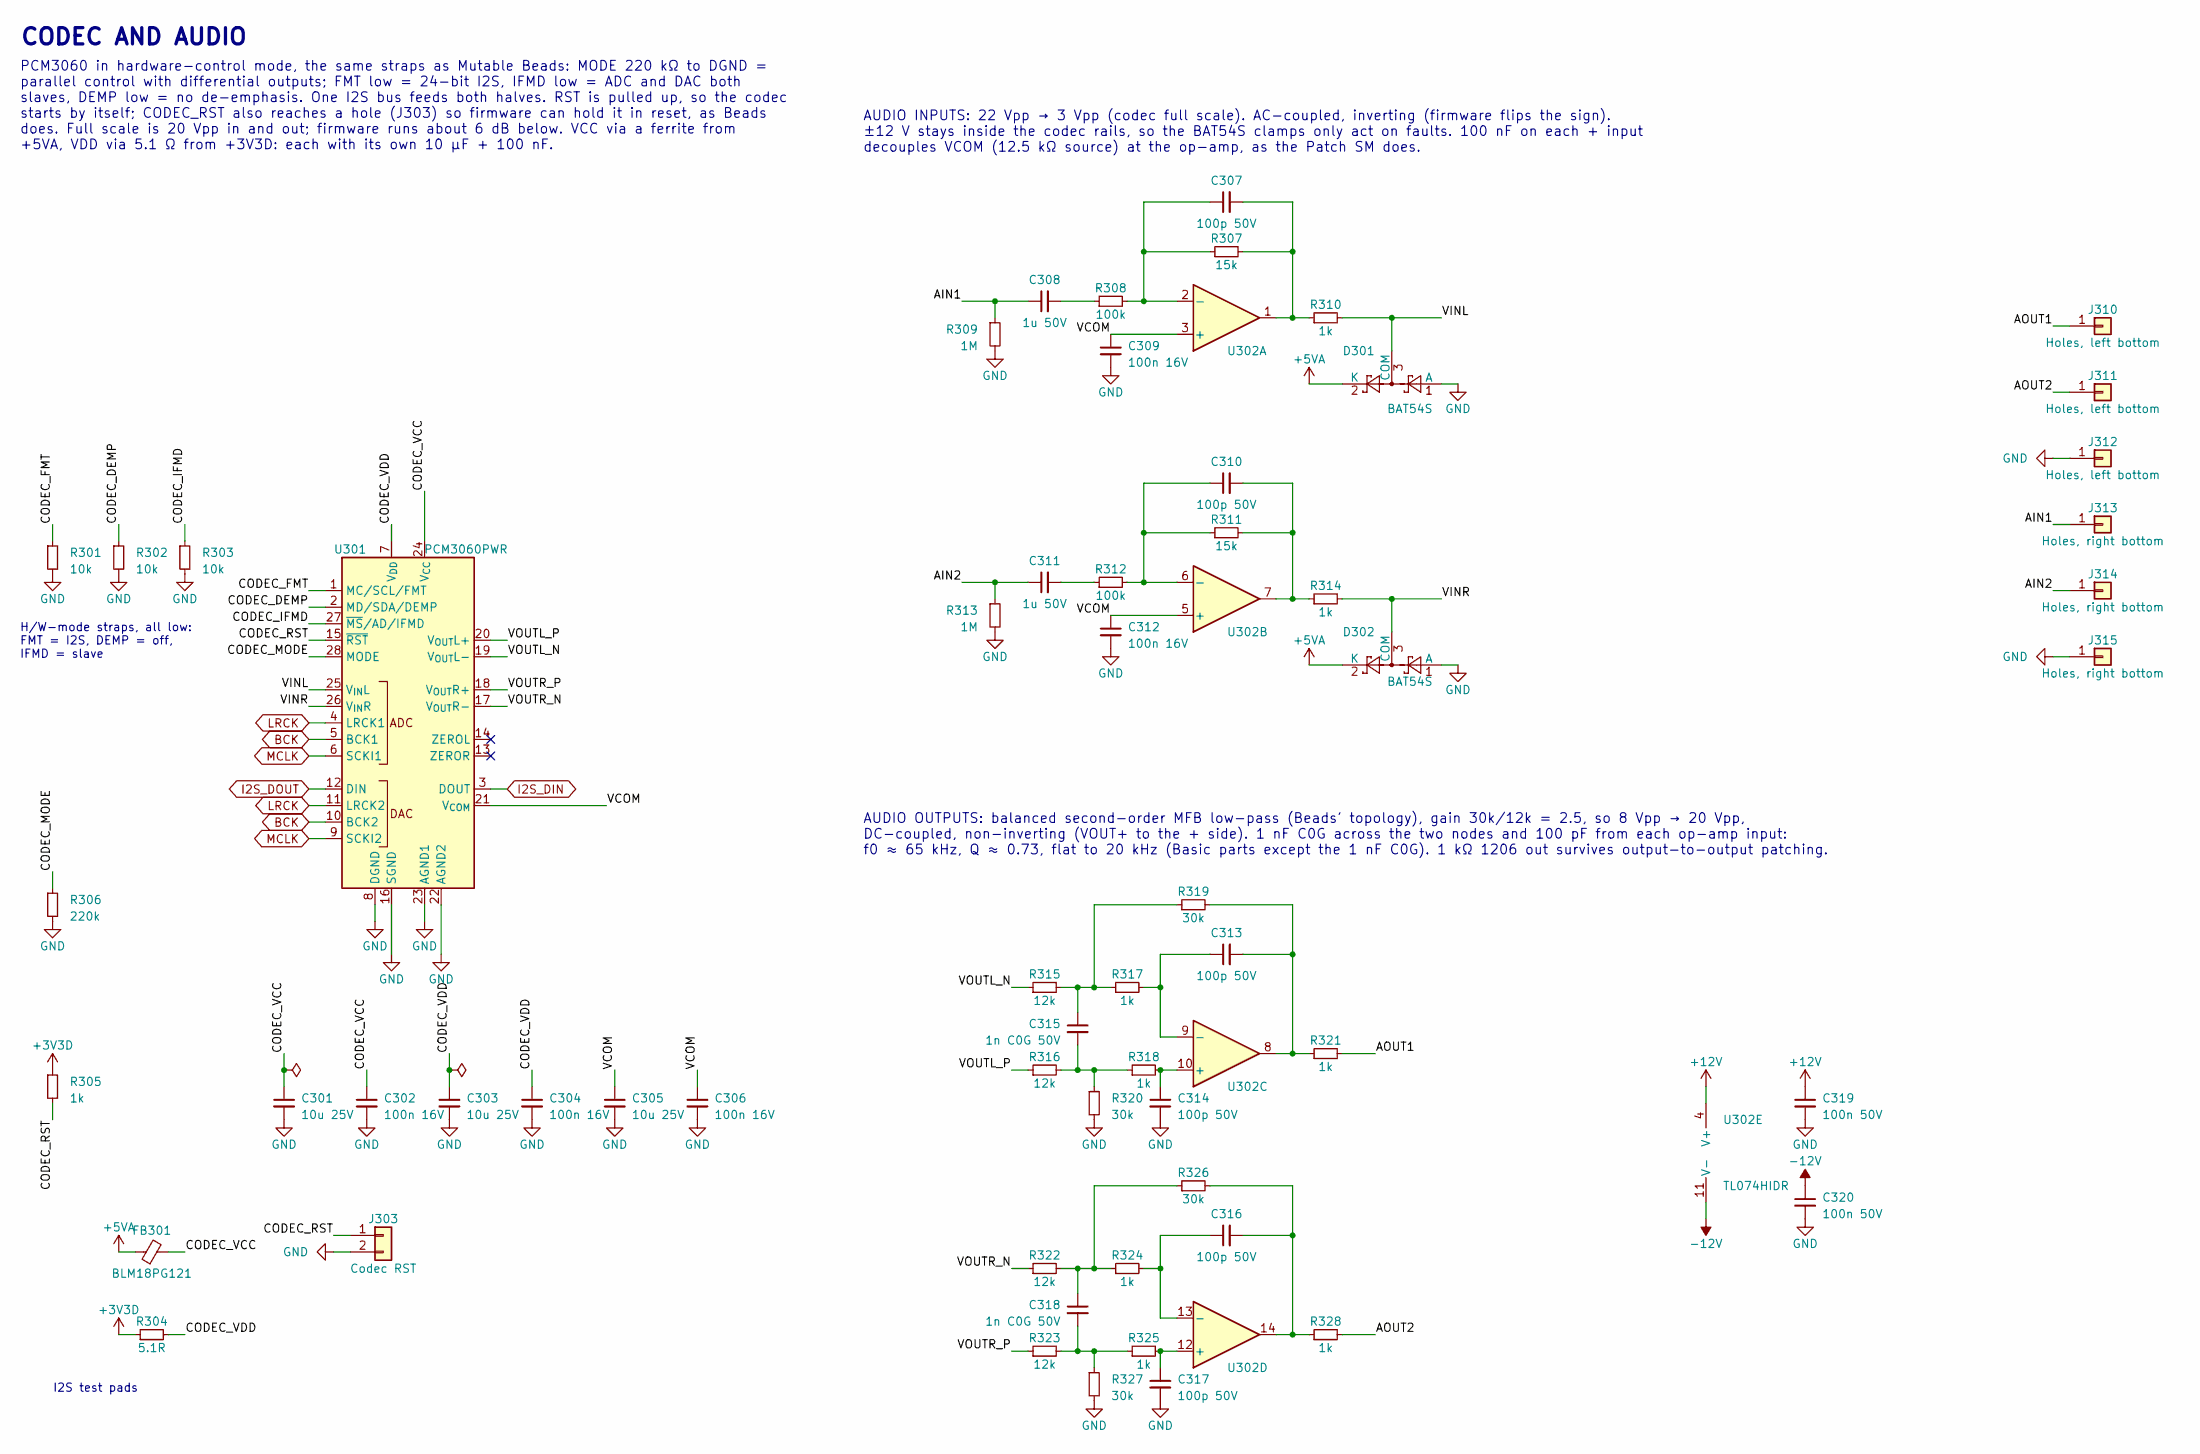
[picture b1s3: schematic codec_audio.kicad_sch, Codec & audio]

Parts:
C301, C303, C305: 10u 25V; C_0805_2012Metric; Voltage 25V; LCSC C15850
C302, C304, C306, C309, C312: 100n 16V; C_0402_1005Metric; Voltage 16V; LCSC C1525
C307, C310, C313, C314, C316, C317: 100p 50V; C_0402_1005Metric; Voltage 50V; LCSC C1546
C308, C311: 1u 50V; C_0805_2012Metric; Voltage 50V; LCSC C28323
C315, C318: 1n C0G 50V; C_0603_1608Metric; Voltage 50V; LCSC C106246
C319, C320: 100n 50V; C_0603_1608Metric; Voltage 50V; LCSC C14663
D301, D302: BAT54S; SOT-23; MPN BAT54S; LCSC C408389
FB301: BLM18PG121; L_0603_1608Metric; MPN BLM18PG121SN1D; LCSC C14709
J303: Codec RST; WiringHoles_1x02_G2; JLC bare holes
J310, J311: Holes, left bottom; WiringHoles_1x01; JLC bare holes
J312: Holes, left bottom; WiringHoles_1x01_G1; JLC bare holes
J313, J314: Holes, right bottom; WiringHoles_1x01; JLC bare holes
J315: Holes, right bottom; WiringHoles_1x01_G1; JLC bare holes
R301, R302, R303: 10k; R_0402_1005Metric; Tolerance 1%; LCSC C25744
R304: 5.1R; R_0603_1608Metric; Tolerance 1%; LCSC C25197
R305, R310, R314, R317, R318, R324, R325: 1k; R_0402_1005Metric; Tolerance 1%; LCSC C11702
R306: 220k; R_0603_1608Metric; Tolerance 1%; LCSC C22961
R307, R311: 15k; R_0402_1005Metric; Tolerance 1%; LCSC C25756
R308, R312: 100k; R_0402_1005Metric; Tolerance 1%; LCSC C25741
R309, R313: 1M; R_0402_1005Metric; Tolerance 1%; LCSC C26083
R315, R316, R322, R323: 12k; R_0402_1005Metric; Tolerance 1%; LCSC C25752
R319, R320, R326, R327: 30k; R_0603_1608Metric; Tolerance 1%; LCSC C22984
R321, R328: 1k; R_1206_3216Metric; Tolerance 1%; LCSC C4410
U301: PCM3060PWR; TSSOP-28_4.4x9.7mm_P0.65mm; MPN PCM3060PWR; LCSC C2651841
U302: TL074HIDR; SOIC-14_3.9x8.7mm_P1.27mm; MPN TL074HIDR; LCSC C2878713

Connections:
+3V3D: R304.1, R305.1; also elsewhere on the board
+5VA: D301.2 (K), D302.2 (K), FB301.1; also elsewhere on the board
+12V: C319.1, U302.4 (V+); also elsewhere on the board
-12V: C320.1, U302.11 (V-); also elsewhere on the board
/Codec & audio/AIN1: C308.1, J313.1, R309.1
/Codec & audio/AIN2: C311.1, J314.1, R313.1
/Codec & audio/AOUT1: J310.1, R321.2
/Codec & audio/AOUT2: J311.1, R328.2
/Codec & audio/CODEC_DEMP: R302.1, U301.2 (MD/SDA/DEMP)
/Codec & audio/CODEC_FMT: R301.1, U301.1 (MC/SCL/FMT)
/Codec & audio/CODEC_IFMD: R303.1, U301.27 (~MS/AD/IFMD)
/Codec & audio/CODEC_MODE: R306.1, U301.28 (MODE)
/Codec & audio/CODEC_RST: J303.1, R305.2, U301.15 (~RST)
/Codec & audio/CODEC_VCC: C301.1, C302.1, FB301.2, U301.24 (V_{CC})
/Codec & audio/CODEC_VDD: C303.1, C304.1, R304.2, U301.7 (V_{DD})
/Codec & audio/VCOM: C305.1, C306.1, C309.1, C312.1, U301.21 (V_{COM}), U302.3 (+), U302.5 (+)
/Codec & audio/VINL: D301.3 (COM), R310.2, U301.25 (V_{IN}L)
/Codec & audio/VINR: D302.3 (COM), R314.2, U301.26 (V_{IN}R)
/Codec & audio/VOUTL_N: R315.1, U301.19 (V_{OUT}L-)
/Codec & audio/VOUTL_P: R316.1, U301.20 (V_{OUT}L+)
/Codec & audio/VOUTR_N: R322.1, U301.17 (V_{OUT}R-)
/Codec & audio/VOUTR_P: R323.1, U301.18 (V_{OUT}R+)
BCK: U301.5 (BCK1), U301.10 (BCK2); also elsewhere on the board
GND: C301.2, C302.2, C303.2, C304.2, C305.2, C306.2, C309.2, C312.2, C314.2, C317.2, C319.2, C320.2, D301.1 (A), D302.1 (A), J303.2, J312.1, J315.1, R301.2, R302.2, R303.2, R306.2, R309.2, R313.2, R320.2, R327.2, U301.8 (DGND), U301.16 (SGND), U301.22 (AGND2), U301.23 (AGND1); also elsewhere on the board
I2S_DIN: U301.3 (DOUT); also elsewhere on the board
I2S_DOUT: U301.12 (DIN); also elsewhere on the board
LRCK: U301.4 (LRCK1), U301.11 (LRCK2); also elsewhere on the board
MCLK: U301.6 (SCKI1), U301.9 (SCKI2); also elsewhere on the board
unnamed: C307.2, R307.2, R310.1, U302.1
unnamed: C308.2, R308.1
unnamed: C310.2, R311.2, R314.1, U302.7
unnamed: C311.2, R312.1
unnamed: C313.2, R319.2, R321.1, U302.8
unnamed: C315.1, R315.2, R317.1, R319.1
unnamed: C315.2, R316.2, R318.1, R320.1
unnamed: C316.2, R326.2, R328.1, U302.14
unnamed: C318.1, R322.2, R324.1, R326.1
unnamed: C318.2, R323.2, R325.1, R327.1
unnamed: C307.1, R307.1, R308.2, U302.2 (-)
unnamed: C310.1, R311.1, R312.2, U302.6 (-)
unnamed: C314.1, R318.2, U302.10 (+)
unnamed: C313.1, R317.2, U302.9 (-)
unnamed: C317.1, R325.2, U302.12 (+)
unnamed: C316.1, R324.2, U302.13 (-)

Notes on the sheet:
CODEC AND AUDIO
PCM3060 in hardware-control mode, the same straps as Mutable Beads: MODE 220 kΩ to DGND = parallel control with differential outputs; FMT low = 24-bit I2S, IFMD low = ADC and DAC both slaves, DEMP low = no de-emphasis. One I2S bus feeds both halves. RST is pulled up, so the codec starts by itself; 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
H/W-mode straps, all low: FMT = I2S, DEMP = off, IFMD = slave
AUDIO INPUTS: 22 Vpp → 3 Vpp (codec full scale). AC-coupled, inverting (firmware flips the sign). ±12 V stays inside the codec rails, so the BAT54S clamps only act on faults. 100 nF on each + input decouples VCOM (12.5 kΩ source) at the op-amp, as the Patch SM does.
AUDIO OUTPUTS: balanced second-order MFB low-pass (Beads' topology), gain 30k/12k = 2.5, so 8 Vpp → 20 Vpp, DC-coupled, non-inverting (VOUT+ to the + side). 1 nF C0G across the two nodes and 100 pF from each op-amp input: f0 ≈ 65 kHz, Q ≈ 0.73, flat to 20 kHz (Basic parts except the 1 nF C0G). 1 kΩ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
I2S test pads

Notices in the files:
hardware/analogue_board/codec_audio.kicad_sch:
Eight4aWish · CC BY-SA 4.0
